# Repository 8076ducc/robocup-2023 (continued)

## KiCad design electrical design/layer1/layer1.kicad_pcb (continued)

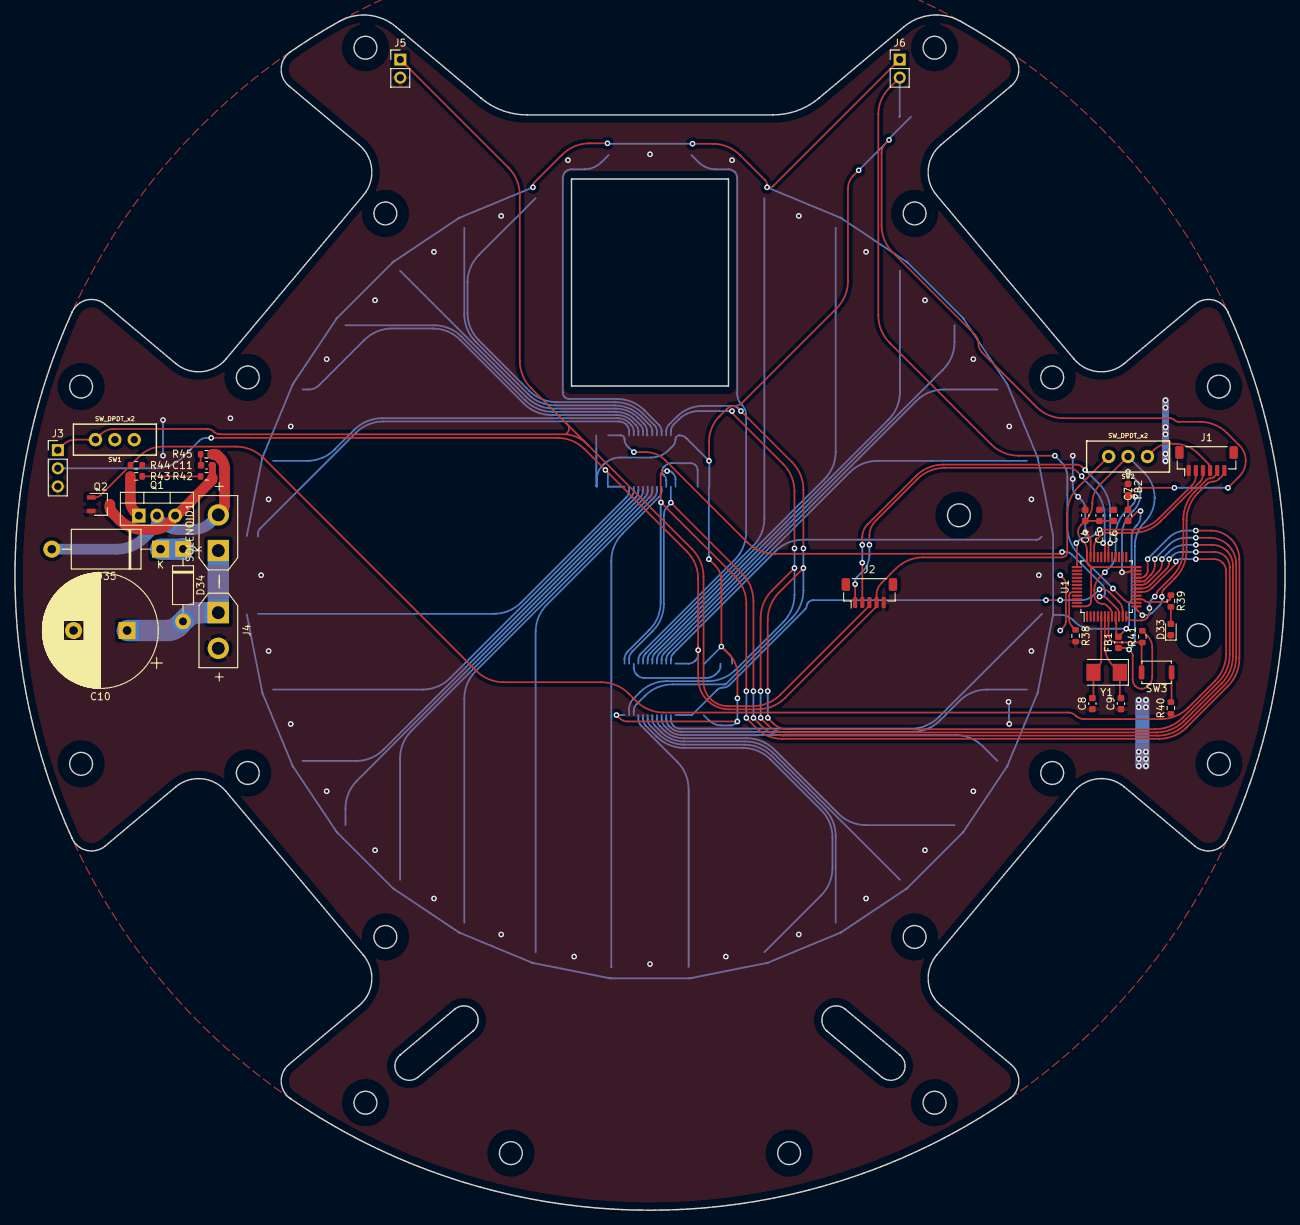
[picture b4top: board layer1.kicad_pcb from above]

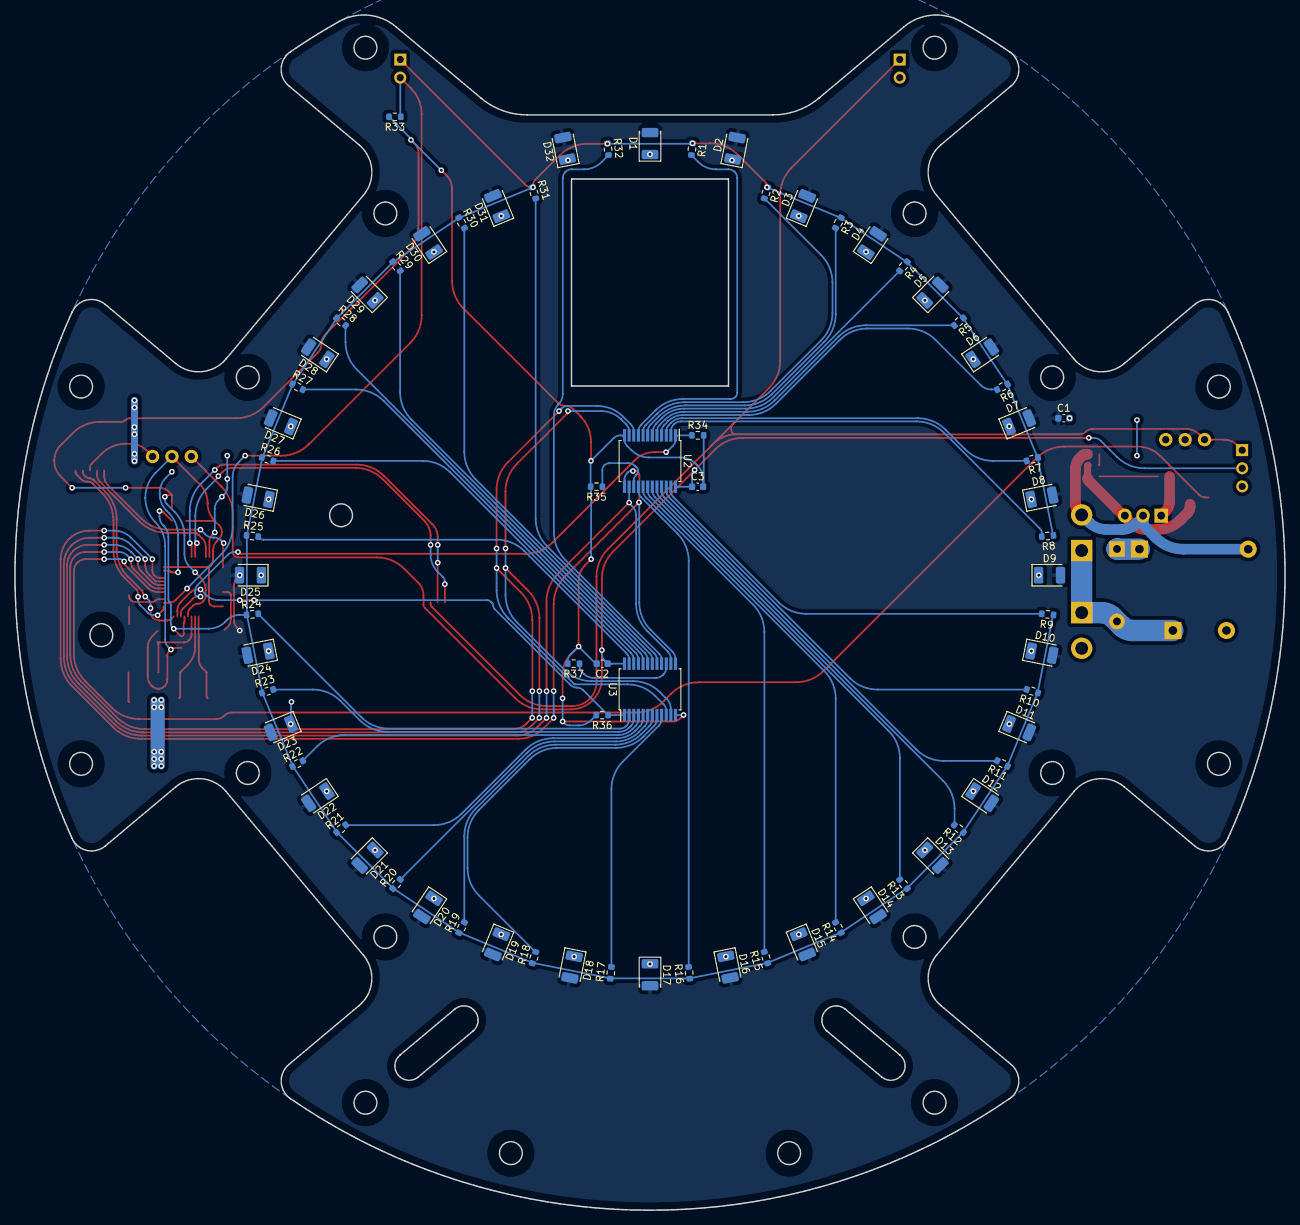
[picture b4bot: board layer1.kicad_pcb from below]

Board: 2 copper layers, 178.0 x 167.5 mm, 109 parts (74 on the bottom side), 70 nets.

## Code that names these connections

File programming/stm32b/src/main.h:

#ifndef main.h
#define main.h

#include <Arduino.h>
#include "../include/config.h"

#define led PB2

#define M1C1 PA0
#define M1C2 PA1
#define M2C1 PA4
#define M2C2 PA5
#define M3C1 PA6
#define M3C2 PA7
#define M4C1 PB0
#define M4C2 PB1

#endif

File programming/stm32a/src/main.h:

#ifndef main.h
#define main.h

#define botA

#include <Arduino.h>

#define led PA5

#define s0 PB0
#define s1 PB1
#define s2 PB2
#define s3 PB10

#define mux1 PA0
#define mux2 PA1
#define lightgate PA4

#define solenoid PA7

#define TEENSY Serial1
#define DEBUG Serial2

#endif

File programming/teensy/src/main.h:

#ifndef main.h
#define main.h

#include <Arduino.h>

#define led 13

#define m1PWM 2
#define m2PWM 3
#define m3PWM 4
#define m4PWM 5
#define lidarPWM 6
#define dribblerPWM 18

#define m1INA 9
#define m2INA 10
#define m3INA 11
#define m4INA 12

#define L1SERIAL Serial1
#define L4SERIAL Serial2
#define IMUSERIAL Serial3
#define BTSERIAL Serial4
#define CAMSERIAL Serial5

#endif

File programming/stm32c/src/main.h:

#ifndef main.h
#define main.h

#include <Arduino.h>

#include <Wire.h>
#include <Adafruit_Sensor.h>
#include <Adafruit_BNO055.h>
#include <utility/imumaths.h>

#define led PC13

#define imuSCL PB6
#define imuSDA PB7
#define imuRST PC13

#define TEENSY Serial1
#define DEBUG Serial2

#endif

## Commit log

2022-08-22 add parent .gitignore
2022-08-22 add child .gitignore (elec)
2022-08-24 add vnh5050a-e library
2022-08-24 complete vnh5050a test board
2022-08-24 start work on layer 1 pcb
2022-08-24 add stm32f103cbt6 library
2022-08-25 finish dribbler plates
2022-08-26 update dribbler plates after changing gear positions
2022-08-27 add roller for 12mm o-ring
2022-08-31 update dribbler motor mount and omniwheel folder
2022-12-02 begin schematic design for layer 1 pcb
2022-12-02 finish stm32f103c8t6 sub-circuit
2022-12-02 add power input to layer 1
2022-12-02 add layer 2 pcb files
2022-12-02 add layer 3 pcb files
2022-12-02 change faulty silkscreen on driver test board
2022-12-04 groundwork for layer 2 pcb
2022-12-04 update layer 1 files
2022-12-04 add teensy 4.0 symbol and footprints
2022-12-04 add omniwheel mesh files
2022-12-05 rename files
2022-12-05 add support for bldc esc
2022-12-05 fix faulty esc connection
2022-12-14 update layer 1 and 3 schematics
2023-01-07 assign footprints and update layer 1 pcb
2023-01-10 add solenoid circuit and custom board rules
2023-01-24 update layer 1 and layer 3 pcbs
2023-01-26 update omniwheel roller and add 2023 motors mounts
2023-01-28 finish finalised VNH5050A breakout board
2023-01-28 update motor mount and roller mesh files
2023-01-28 add driver board design pdfs
2023-01-29 finalise l4 sch, start draft of l4 pcb
2023-01-29 add layer 1 pcb rules
2023-01-29 increase size of driver output polygon
2023-01-29 almost final layer 3 pcb design
2023-01-29 add symbol and footprint libraries
2023-01-29 add sparkfun and teensy libraries
2023-02-03 update l1, l3, and driver pcbs
2023-02-03 add xt30pw-m kicad library
2023-02-05 almost final pcbs
2023-02-05 add teensy library
2023-02-12 production ready layer 4!
2023-02-12 rename all layer 4 files to layer 5
2023-02-15 add pcb cutouts
2023-02-15 production-ready layer 1!
2023-02-24 submit all pcbs for production
2023-04-07 teensy program files
2023-04-07 layer 1 stm32 program files
2023-04-07 layer 2 stm32 (1) program files
2023-04-07 layer 2 stm32 (2) program files
2023-04-07 update omniwheel design files
2023-04-10 add rpi datasheets
2023-04-10 update board outline files
2023-04-12 get bno055 working
2023-04-13 remove redundant code
2023-04-13 mostly complete light detection program
2023-04-14 complete basic goalie movement
2023-04-17 fillet pcb traces
